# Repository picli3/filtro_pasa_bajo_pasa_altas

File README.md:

# Filtro pasa medios y pasa altos

Este filtro aun esta en proceso de desarrollo, no me hago responsable de algunos problemas ocacionados, estare subiendo aca los vanaces hasta cerrar el proyecto, eres libre de copiar el proyecto y modificarlo siempre y cuando hagas mension del origen de la informacion.

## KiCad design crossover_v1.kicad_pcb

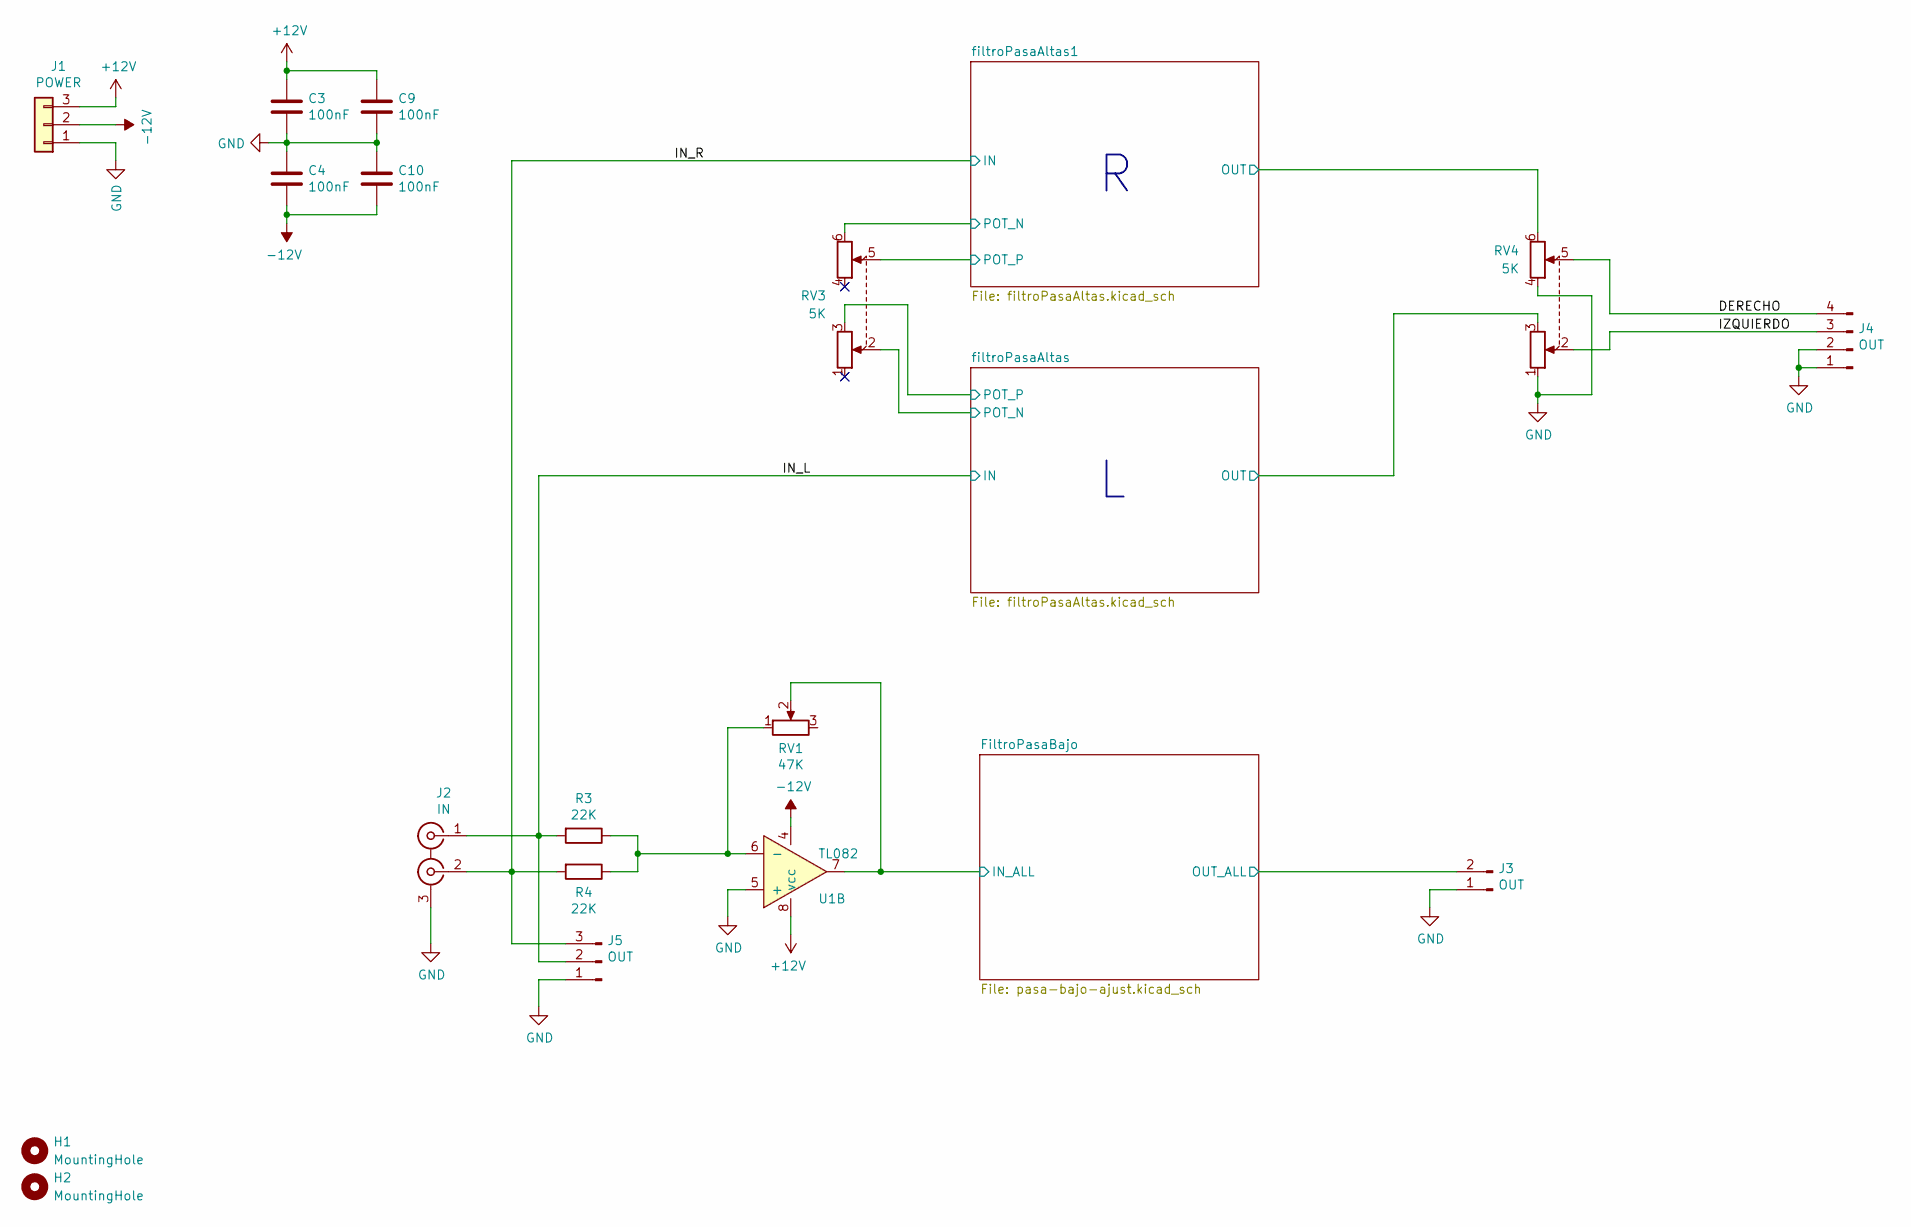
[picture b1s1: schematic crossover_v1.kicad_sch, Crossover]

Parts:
C3, C4, C9, C10: 100nF; C_Disc_D4.3mm_W1.9mm_P5.00mm
H1, H2: MountingHole; MountingHole_3.2mm_M3_DIN965_Pad
J1: POWER; PinHeader_1x03_P2.54mm_Vertical
J2: IN; CUI_RCJ-21XX
J3: OUT; PinHeader_1x02_P2.54mm_Vertical
J4: OUT; PinHeader_1x04_P2.54mm_Vertical
J5: OUT; PinHeader_1x03_P2.54mm_Vertical
R3, R4: 22K; R_Axial_DIN0207_L6.3mm_D2.5mm_P10.16mm_Horizontal
RV1: 47K; Potentiometer_Piher_T-16H_Single_Horizontal
RV3, RV4: 5K; Potentiometer_Alps_RK163_Dual_Horizontal
U1: TL082; DIP-8_W7.62mm_LongPads

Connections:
+12V: C3.2, C9.2, J1.3, U1.8 (vcc); also elsewhere on the board
-12V: C4.1, C10.1, J1.2, U1.4; also elsewhere on the board
/DERECHO: J4.4, RV4.5
/FiltroPasaBajo/IN_ALL: RV1.2, U1.7; also elsewhere on the board
/FiltroPasaBajo/OUT_ALL: J3.2; also elsewhere on the board
/IN_L: J2.1 (IN1), J5.2, R3.2; also elsewhere on the board
/IN_R: J2.2 (IN2), J5.3, R4.2; also elsewhere on the board
/IZQUIERDO: J4.3, RV4.2
/filtroPasaAltas1/OUT: RV4.6; also elsewhere on the board
/filtroPasaAltas1/POT_N: RV3.6; also elsewhere on the board
/filtroPasaAltas1/POT_P: RV3.5; also elsewhere on the board
/filtroPasaAltas/OUT: RV4.3; also elsewhere on the board
/filtroPasaAltas/POT_N: RV3.2; also elsewhere on the board
/filtroPasaAltas/POT_P: RV3.3; also elsewhere on the board
GND: C3.1, C4.2, C9.1, C10.2, J1.1, J2.3 (EXT), J3.1, J4.1, J4.2, J5.1, RV4.1, RV4.4, U1.5 (+); also elsewhere on the board
unnamed: R3.1, R4.1, RV1.1, U1.6 (-)

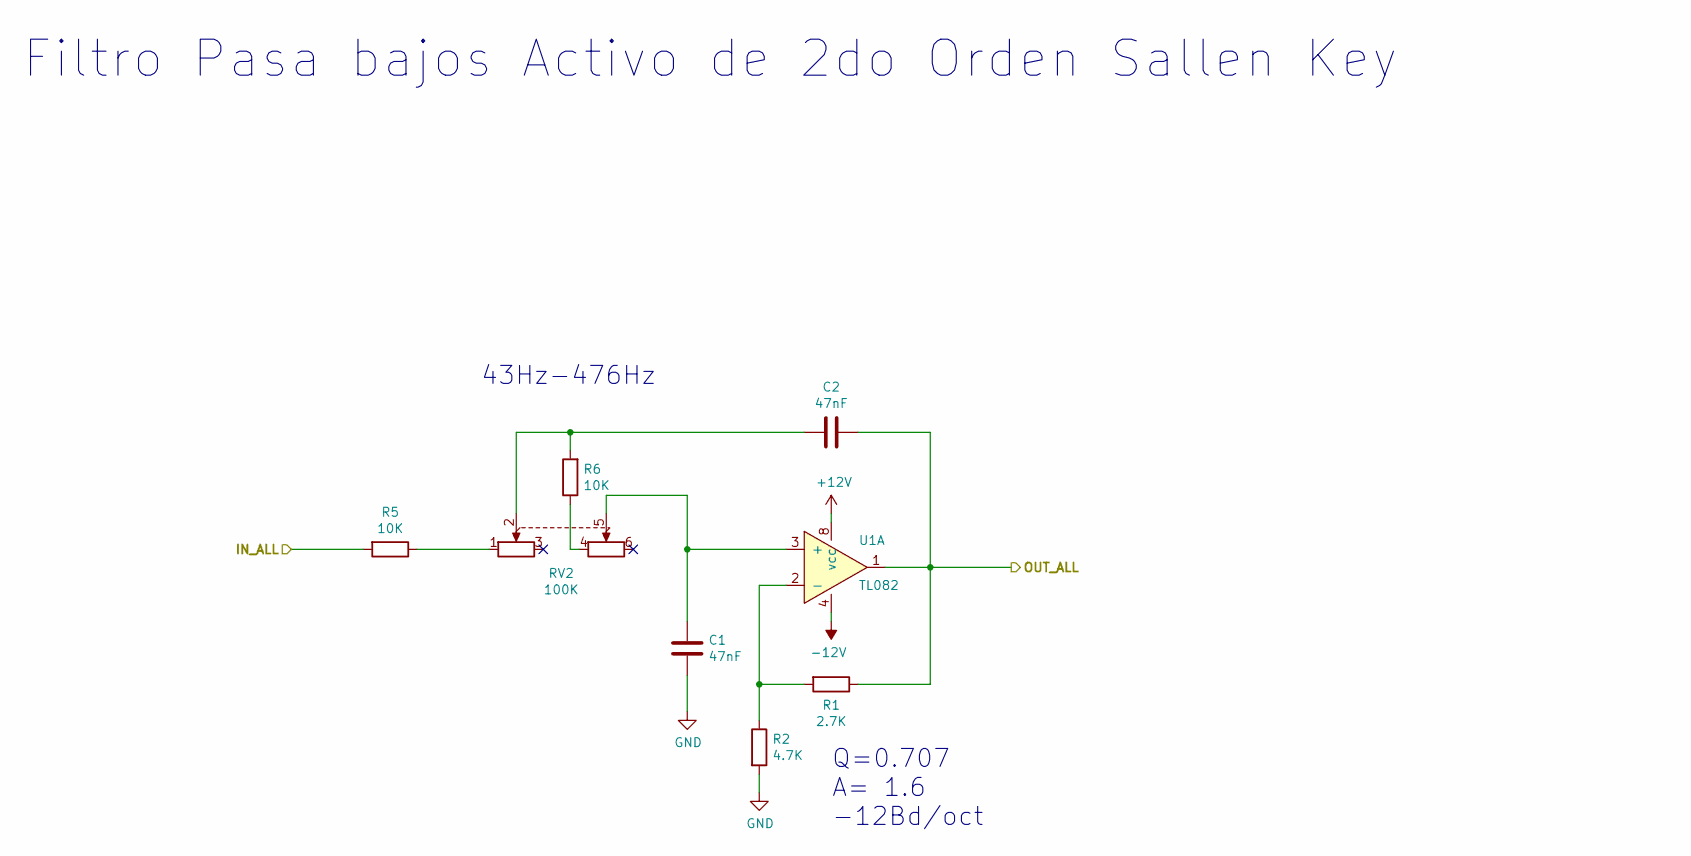
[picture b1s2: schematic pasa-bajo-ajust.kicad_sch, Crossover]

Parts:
C1, C2: 47nF; C_Disc_D4.3mm_W1.9mm_P5.00mm
R1: 2.7K; R_Axial_DIN0207_L6.3mm_D2.5mm_P10.16mm_Horizontal
R2: 4.7K; R_Axial_DIN0207_L6.3mm_D2.5mm_P10.16mm_Horizontal
R5, R6: 10K; R_Axial_DIN0207_L6.3mm_D2.5mm_P10.16mm_Horizontal
RV2: 100K; Potentiometer_Alps_RK163_Dual_Horizontal
U1: TL082; DIP-8_W7.62mm_LongPads

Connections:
+12V: U1.8 (vcc); also elsewhere on the board
-12V: U1.4; also elsewhere on the board
/FiltroPasaBajo/IN_ALL: R5.2; also elsewhere on the board
/FiltroPasaBajo/OUT_ALL: C2.1, R1.1, U1.1; also elsewhere on the board
GND: C1.1, R2.2; also elsewhere on the board
unnamed: C1.2, RV2.5, U1.3 (+)
unnamed: C2.2, R6.2, RV2.2
unnamed: R1.2, R2.1, U1.2 (-)
unnamed: R5.1, RV2.1
unnamed: R6.1, RV2.4

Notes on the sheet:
Filtro Pasa bajos Activo de 2do Orden Sallen Key
Q=0.707 A= 1.6 -12Bd/oct
43Hz-476Hz

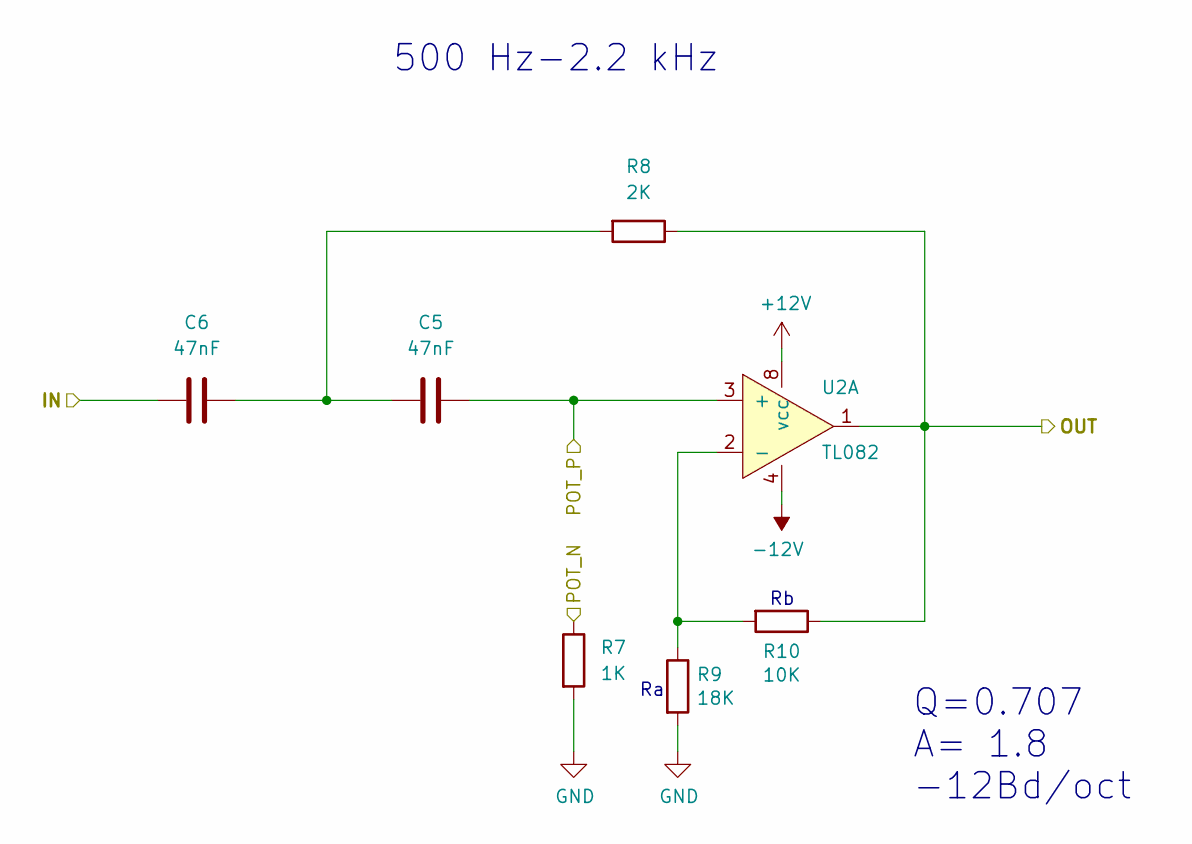
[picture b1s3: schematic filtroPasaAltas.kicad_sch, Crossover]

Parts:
C5, C6: 47nF; C_Disc_D4.3mm_W1.9mm_P5.00mm
R7: 1K; R_Axial_DIN0207_L6.3mm_D2.5mm_P10.16mm_Horizontal
R8: 2K; R_Axial_DIN0207_L6.3mm_D2.5mm_P10.16mm_Horizontal
R9: 18K; R_Axial_DIN0207_L6.3mm_D2.5mm_P10.16mm_Horizontal
R10: 10K; R_Axial_DIN0207_L6.3mm_D2.5mm_P10.16mm_Horizontal
U2: TL082; DIP-8_W7.62mm_LongPads

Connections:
+12V: U2.8 (vcc); also elsewhere on the board
-12V: U2.4; also elsewhere on the board
/IN_R: C6.2; also elsewhere on the board
/filtroPasaAltas1/OUT: R8.1, R10.1, U2.1; also elsewhere on the board
/filtroPasaAltas1/POT_N: R7.1; also elsewhere on the board
/filtroPasaAltas1/POT_P: C5.1, U2.3 (+); also elsewhere on the board
/filtroPasaAltas/OUT: U2.7; also elsewhere on the board
/filtroPasaAltas/POT_P: U2.5 (+); also elsewhere on the board
GND: R7.2, R9.2; also elsewhere on the board
unnamed: C5.2, C6.1, R8.2
unnamed: R9.1, R10.2, U2.2 (-)
unnamed 24: U2.6 (-); also elsewhere on the board

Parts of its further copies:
C7, C8: 47nF; C_Disc_D4.3mm_W1.9mm_P5.00mm
R11: 1K; R_Axial_DIN0207_L6.3mm_D2.5mm_P10.16mm_Horizontal
R12: 2K; R_Axial_DIN0207_L6.3mm_D2.5mm_P10.16mm_Horizontal
R13: 18K; R_Axial_DIN0207_L6.3mm_D2.5mm_P10.16mm_Horizontal
R14: 10K; R_Axial_DIN0207_L6.3mm_D2.5mm_P10.16mm_Horizontal

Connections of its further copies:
/IN_L: C8.2; also elsewhere on the board
/filtroPasaAltas/OUT: R12.1, R14.1; also elsewhere on the board
/filtroPasaAltas/POT_N: R11.1; also elsewhere on the board
/filtroPasaAltas/POT_P: C7.1; also elsewhere on the board
GND: R11.2, R13.2; also elsewhere on the board
unnamed: C7.2, C8.1, R12.2
unnamed 24: R13.1, R14.2; also elsewhere on the board

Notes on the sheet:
Q=0.707 A= 1.8 -12Bd/oct
500 Hz-2.2 kHz

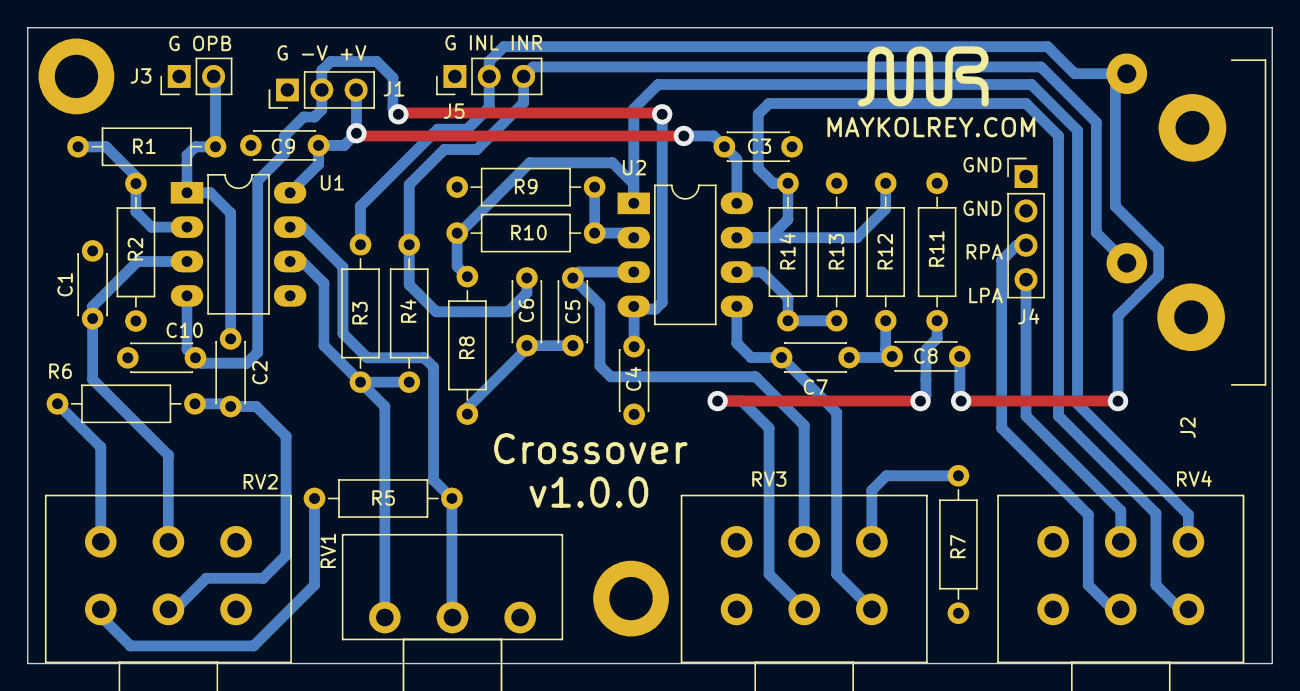
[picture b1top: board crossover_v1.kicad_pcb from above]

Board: 2 copper layers, 92.0 x 47.0 mm, 37 parts (0 on the bottom side), 25 nets.

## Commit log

2021-11-12 agregando el primer commit, proyecto sin probar
2021-11-23 agregando control de volumen de medios, corrigiendo espacio de potenciometro doble
2021-11-26 Create License
    Se agrega licencia GPL para que el proyecto se pueda distribuir bajo los conceptos de la misma licencia
2021-11-26 Update issue templates
2023-10-08 agregando archivos pdf
2024-07-11 cambiando a kicad 8
2025-01-30 cambiando la forma de los archivos del sistema
